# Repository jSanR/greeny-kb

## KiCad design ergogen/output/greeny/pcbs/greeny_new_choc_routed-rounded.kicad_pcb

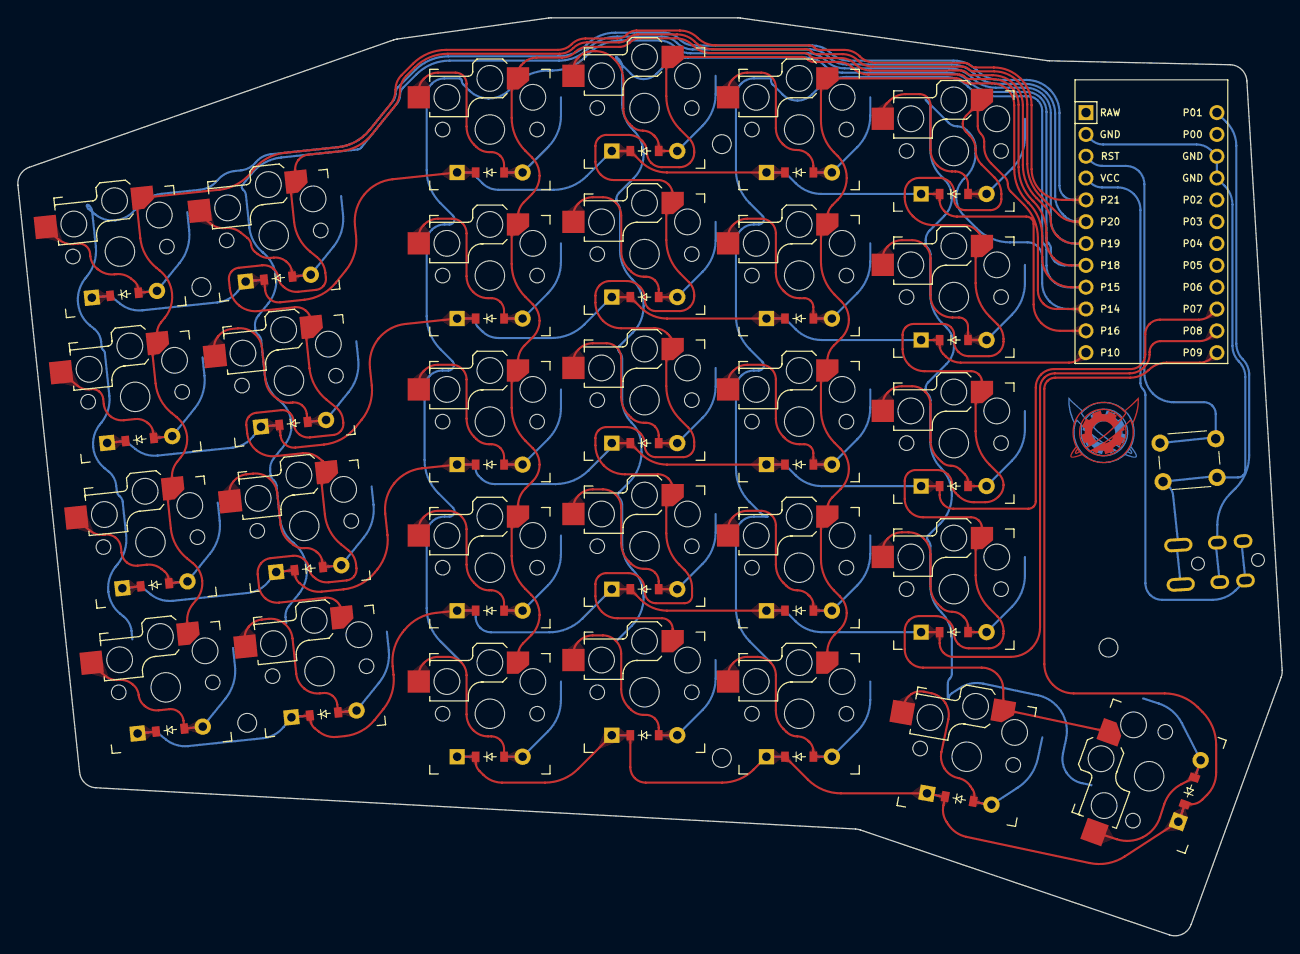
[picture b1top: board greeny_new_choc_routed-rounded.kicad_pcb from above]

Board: 2 copper layers, 147.2 x 106.8 mm, 66 parts (0 on the bottom side), 44 nets.

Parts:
D1, D2, D3, D4, D5, D6, D7, D8, D9, D10, D11, D12, D13, D14, D15, D16, D17, D18, D19, D20, D21, D22, D23, D24, D25, D26, D27, D28, D29: ComboDiode
MCU1: ProMicro
MH1, MH2, MH3, MH4, MH5: mounting_hole_npth
RST1: tht_switch
S1, S2, S3, S4, S5, S6, S7, S8, S9, S10, S11, S12, S13, S14, S15, S16, S17, S18, S19, S20, S21, S22, S23, S24, S25, S26, S27, S28, S29: PG1350
TRRS1: trrs_pj320a (reversible, symmetric)

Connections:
GND: MCU1.2, MCU1.15, MCU1.16, RST1.2, TRRS1.4
P1: MCU1.13, TRRS1.3
P7: D2.1, D6.1, D11.1, D16.1, D21.1, D25.1, MCU1.22
P8: D1.1, D5.1, D10.1, D15.1, D20.1, D24.1, MCU1.23
P9: D9.1, D14.1, D19.1, D28.1, D29.1, MCU1.24
P10: D3.1, D7.1, D12.1, D17.1, D22.1, D26.1, MCU1.12
P14: MCU1.10, S24.1, S25.1, S26.1, S27.1, S28.1, S29.1
P15: MCU1.9, S19.1, S20.1, S21.1, S22.1, S23.1
P16: D4.1, D8.1, D13.1, D18.1, D23.1, D27.1, MCU1.11
P18: MCU1.8, S14.1, S15.1, S16.1, S17.1, S18.1
P19: MCU1.7, S9.1, S10.1, S11.1, S12.1, S13.1
P20: MCU1.6, S5.1, S6.1, S7.1, S8.1
P21: MCU1.5, S1.1, S2.1, S3.1, S4.1
RST: MCU1.3, RST1.1
VCC: MCU1.4, TRRS1.2
index_bottom: D20.2, S20.2
index_home: D21.2, S21.2
index_mod: D19.2, S19.2
index_numbers: D23.2, S23.2
index_top: D22.2, S22.2
inner_bottom: D24.2, S24.2
inner_home: D25.2, S25.2
inner_numbers: D27.2, S27.2
inner_top: D26.2, S26.2
layer_cluster: D28.2, S28.2
middle_bottom: D15.2, S15.2
middle_home: D16.2, S16.2
middle_mod: D14.2, S14.2
middle_numbers: D18.2, S18.2
middle_top: D17.2, S17.2
outer_bottom: D1.2, S1.2
outer_home: D2.2, S2.2
outer_numbers: D4.2, S4.2
outer_top: D3.2, S3.2
pinky_bottom: D5.2, S5.2
pinky_home: D6.2, S6.2
pinky_numbers: D8.2, S8.2
pinky_top: D7.2, S7.2
ring_bottom: D10.2, S10.2
ring_home: D11.2, S11.2
ring_mod: D9.2, S9.2
ring_numbers: D13.2, S13.2
ring_top: D12.2, S12.2
space_cluster: D29.2, S29.2

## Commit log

2025-04-12 Inital commit (Full ergogen config + base qmk config)
2025-04-12 Update metadata & readme
2025-04-12 Update readme and qmk config (with default keymap)
2025-04-12 Update readme formatting
2025-04-12 Update codeblock in readme
2025-04-13 Fix typos in readme
2025-04-17 Add homerow mods and initial navigation layer
2025-05-10 Finish configuring base firmware
2025-05-10 Update keymap
2025-05-11 Update keymap layers
2025-05-11 Update nav layer
2025-05-22 Added tap dance for accented vowels
2025-05-28 Add combo for symbols layer and fix caps word with tap dance
2025-05-28 Support accents with upercase for vowels tap dance
2025-06-07 Layout changes
2025-06-07 Use enter key as symbol layer change
2025-06-09 Add symbols + design cover 1st iteration
2025-06-11 Add support for repeating tap dance keys when holding
2025-06-29 Add initial autoshift support
2025-09-24 Remove cadet shift from games layer
2025-10-08 Add retro shift for homerow mods and combo to open terminal
2025-10-23 Add autoshift-like support for accent vowels tap dance
2025-11-19 Add v1 of digital drawing layer
